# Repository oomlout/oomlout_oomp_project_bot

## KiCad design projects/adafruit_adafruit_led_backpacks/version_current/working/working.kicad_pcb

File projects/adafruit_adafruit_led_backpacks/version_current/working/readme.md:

# OOMP Project  
## Adafruit-LED-Backpacks  by adafruit  
  
oomp key: oomp_projects_flat_adafruit_adafruit_led_backpacks  
(snippet of original readme)  
  
- Adafruit LED Matrix backpacks PCBs  
  
&nbsp;   
&nbsp;   
&nbsp;   
<br />  
&nbsp;   
&nbsp;   
&nbsp;   
<br />  
  
What's better than a single LED? Lots of LEDs! A fun way to make a small display is to use an 8x8 matrix or a 4-digit 7-segment display. Matrices like these are 'multiplexed' - so to control all the seven-segment LEDs you need 14 pins. That's a lot of pins, and there are driver chips like the MAX7219 that can control a matrix for you but there's a lot of wiring to set up and they take up a ton of space. Here at Adafruit we feel your pain! After all, wouldn't it be awesome if you could control a matrix without tons of wiring? That's where these adorable LED matrix backpacks come in. We have  
  full source readme at [readme_src.md](readme_src.md)  
  
source repo at: [https://github.com/adafruit/Adafruit-LED-Backpacks](https://github.com/adafruit/Adafruit-LED-Backpacks)  
## Board  

## Schematic  

[schematic pdf](working_schematic.pdf)  
## Images

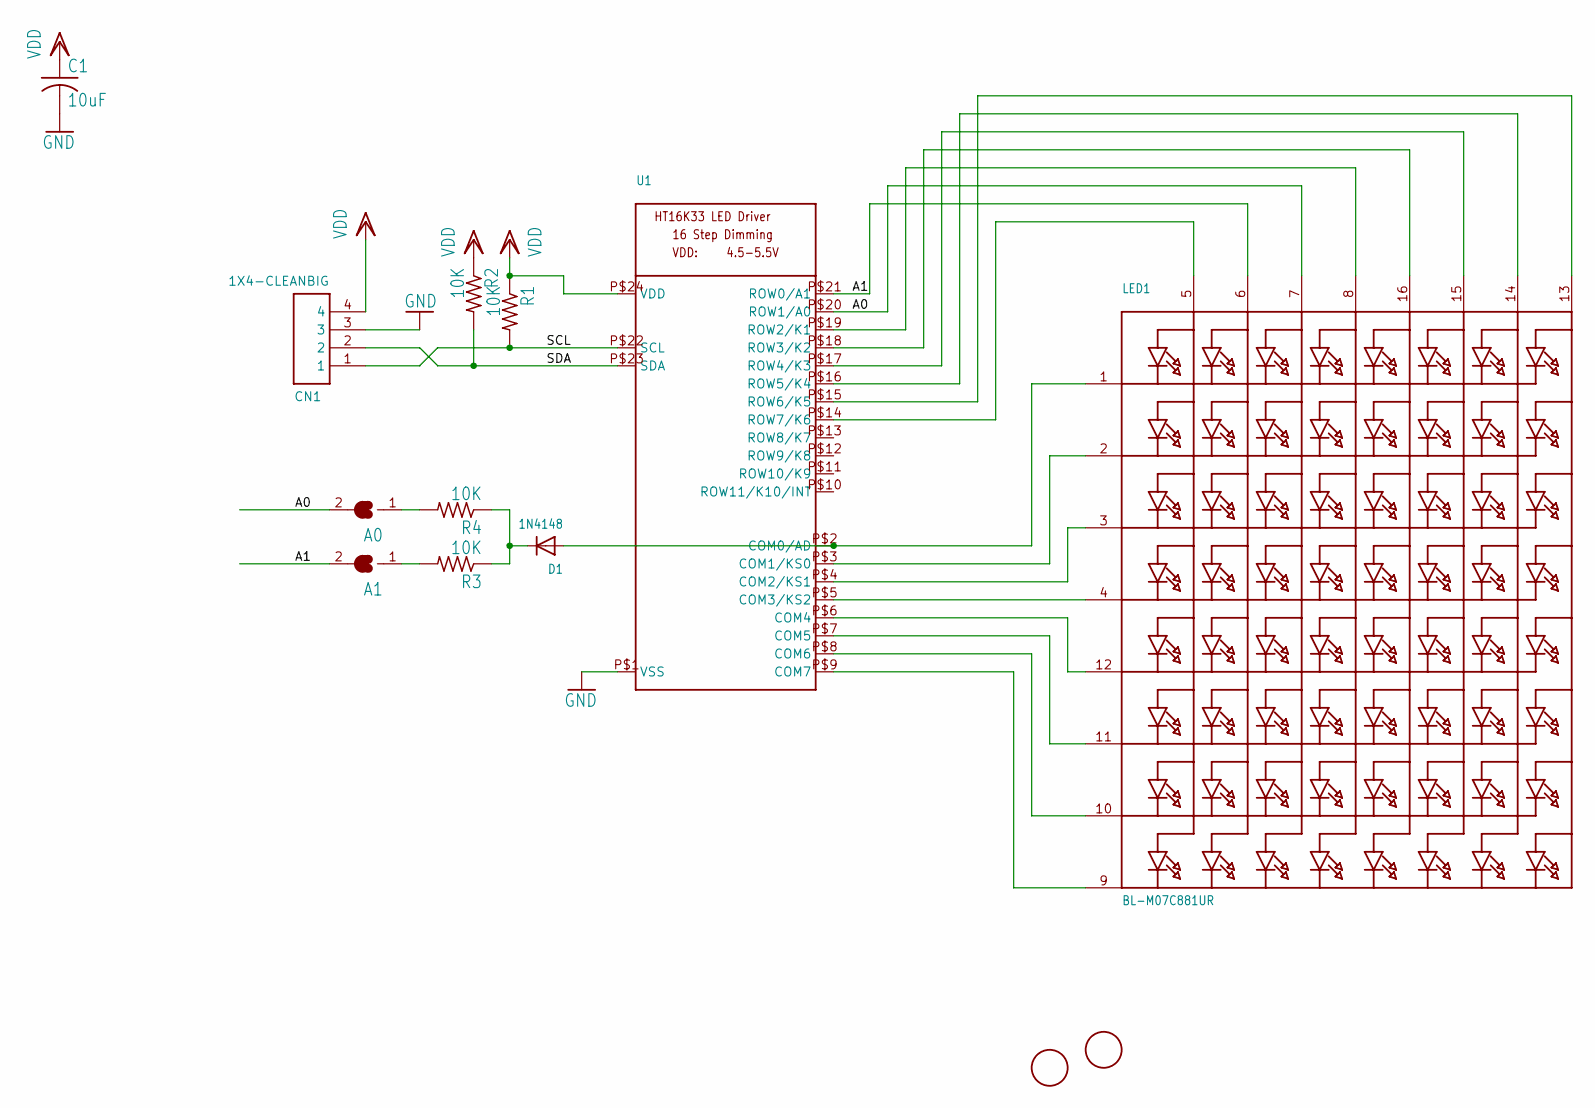
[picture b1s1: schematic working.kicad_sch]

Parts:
A0, A1: SOLDERJUMPERREFLOW_NOPASTE; SOLDERJUMPER_REFLOW_NOPASTE
C1: 10uF; C0805
CN1: 1X4-CLEANBIG; 1X04-CLEANBIG
D1: 1N4148; SOD-323F
LED1: BL-M07C881UR; SEGMENT_BL-M07C881UR
R1, R2, R3, R4: 10K; R0805
U1: HT16K33_SOP24; SOP24_300MIL
U$1, U$2: FIDUCIAL; FIDUCIAL_1MM

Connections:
A0: A0.2, LED1.7 (A3), U1.P$20 (ROW1/A0)
A1: A1.2, LED1.6 (A2), U1.P$21 (ROW0/A1)
GND: C1.2, CN1.3, U1.P$1 (VSS)
unnamed: LED1.9 (K8), U1.P$9 (COM7)
unnamed: LED1.10 (K7), U1.P$8 (COM6)
unnamed: LED1.11 (K6), U1.P$7 (COM5)
unnamed: LED1.12 (K5), U1.P$6 (COM4)
unnamed: LED1.4 (K4), U1.P$5 (COM3/KS2)
unnamed: LED1.3 (K3), U1.P$4 (COM2/KS1)
unnamed: LED1.2 (K2), U1.P$3 (COM1/KS0)
unnamed: D1.A, LED1.1 (K1), U1.P$2 (COM0/AD)
unnamed: LED1.8 (A4), U1.P$19 (ROW2/K1)
unnamed: LED1.16 (A5), U1.P$18 (ROW3/K2)
unnamed: LED1.15 (A6), U1.P$17 (ROW4/K3)
unnamed: D1.C, R3.1, R4.1
unnamed: LED1.5 (A1), U1.P$14 (ROW7/K6)
unnamed: A1.1, R3.2
unnamed: A0.1, R4.2
SCL: CN1.1, R1.2, U1.P$22 (SCL)
SDA: CN1.2, R2.2, U1.P$23 (SDA)
SEG_F: LED1.14 (A7), U1.P$16 (ROW5/K4)
SEG_G: LED1.13 (A8), U1.P$15 (ROW6/K5)
VDD: C1.1, CN1.4, R1.1, R2.1, U1.P$24 (VDD)

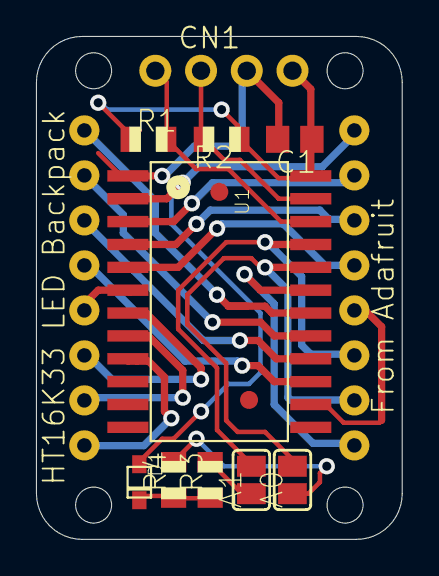
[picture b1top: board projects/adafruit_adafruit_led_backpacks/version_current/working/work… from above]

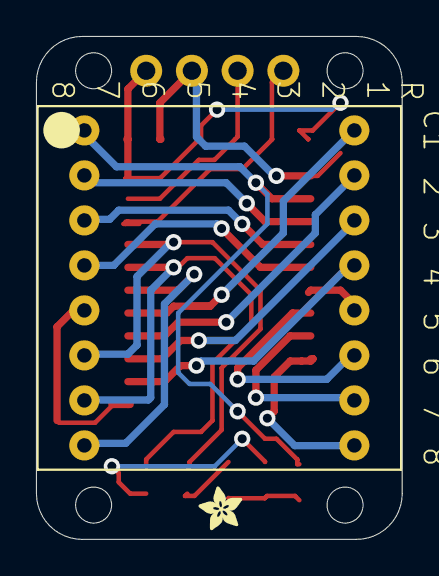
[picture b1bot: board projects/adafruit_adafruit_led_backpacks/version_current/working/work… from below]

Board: 16 copper layers, 20.3 x 27.9 mm, 18 parts (2 on the bottom side), 23 nets.

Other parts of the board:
@HOLE0, @HOLE1, @HOLE2, @HOLE3: (no value)
U$4: ADAFRUIT_2.5MM

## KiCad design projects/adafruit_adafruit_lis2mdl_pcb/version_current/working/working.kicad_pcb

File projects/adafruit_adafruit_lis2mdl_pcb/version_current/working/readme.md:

# OOMP Project  
## Adafruit-LIS2MDL-PCB  by adafruit  
  
oomp key: oomp_projects_flat_adafruit_adafruit_lis2mdl_pcb  
(snippet of original readme)  
  
-- Adafruit LIS2MDL 3-Axis Magnetometer PCB  
  
<a href="http://www.adafruit.com/products/4488"><br/>  
Click here to purchase one from the Adafruit shop</a>  
  
PCB files for the Adafruit LIS2MDL 3-Axis Magnetometer.   
  
Format is EagleCAD schematic and board layout  
* https://www.adafruit.com/product/4488  
  
--- Description  
  
Sense the magnetic fields that surround us with this handy triple-axis magnetometer (compass) module. Magnetometers can sense where the strongest magnetic force is coming from, generally used to detect magnetic north, but can also be used for measuring magnetic fields. This sensor tends to be paired with a 6-DoF (degree of freedom) accelerometer/gyroscope to create a 9-DoF inertial measurement unit that can detect its orientation in real-space thanks to Earth's stable magnetic field. It's a great match for any of our 6-DoF IMU sensors such as the LSM6DSOX or LSM6DS33.  
  
--- License  
  
Adafruit invests time and resources providing this open source design, please support Adafruit and open-source hardware by purchasing products from [Adafruit](https://www.adafruit.com)!  
  
Designed by Limor Fried/Ladyada for Adafruit Industries.  
  
Creative Commons Attribution/Share-Alike, all text above must be included in any redistribution.   
See license.txt for additional details.  
  
  full source readme at [readme_src.md](readme_src.md)  
  
source repo at: [https://github.com/adafruit/Adafruit-LIS2MDL-PCB](https://github.com/adafruit/Adafruit-LIS2MDL-PCB)  
## Board  

## Schematic  

[schematic pdf](working_schematic.pdf)  
## Images

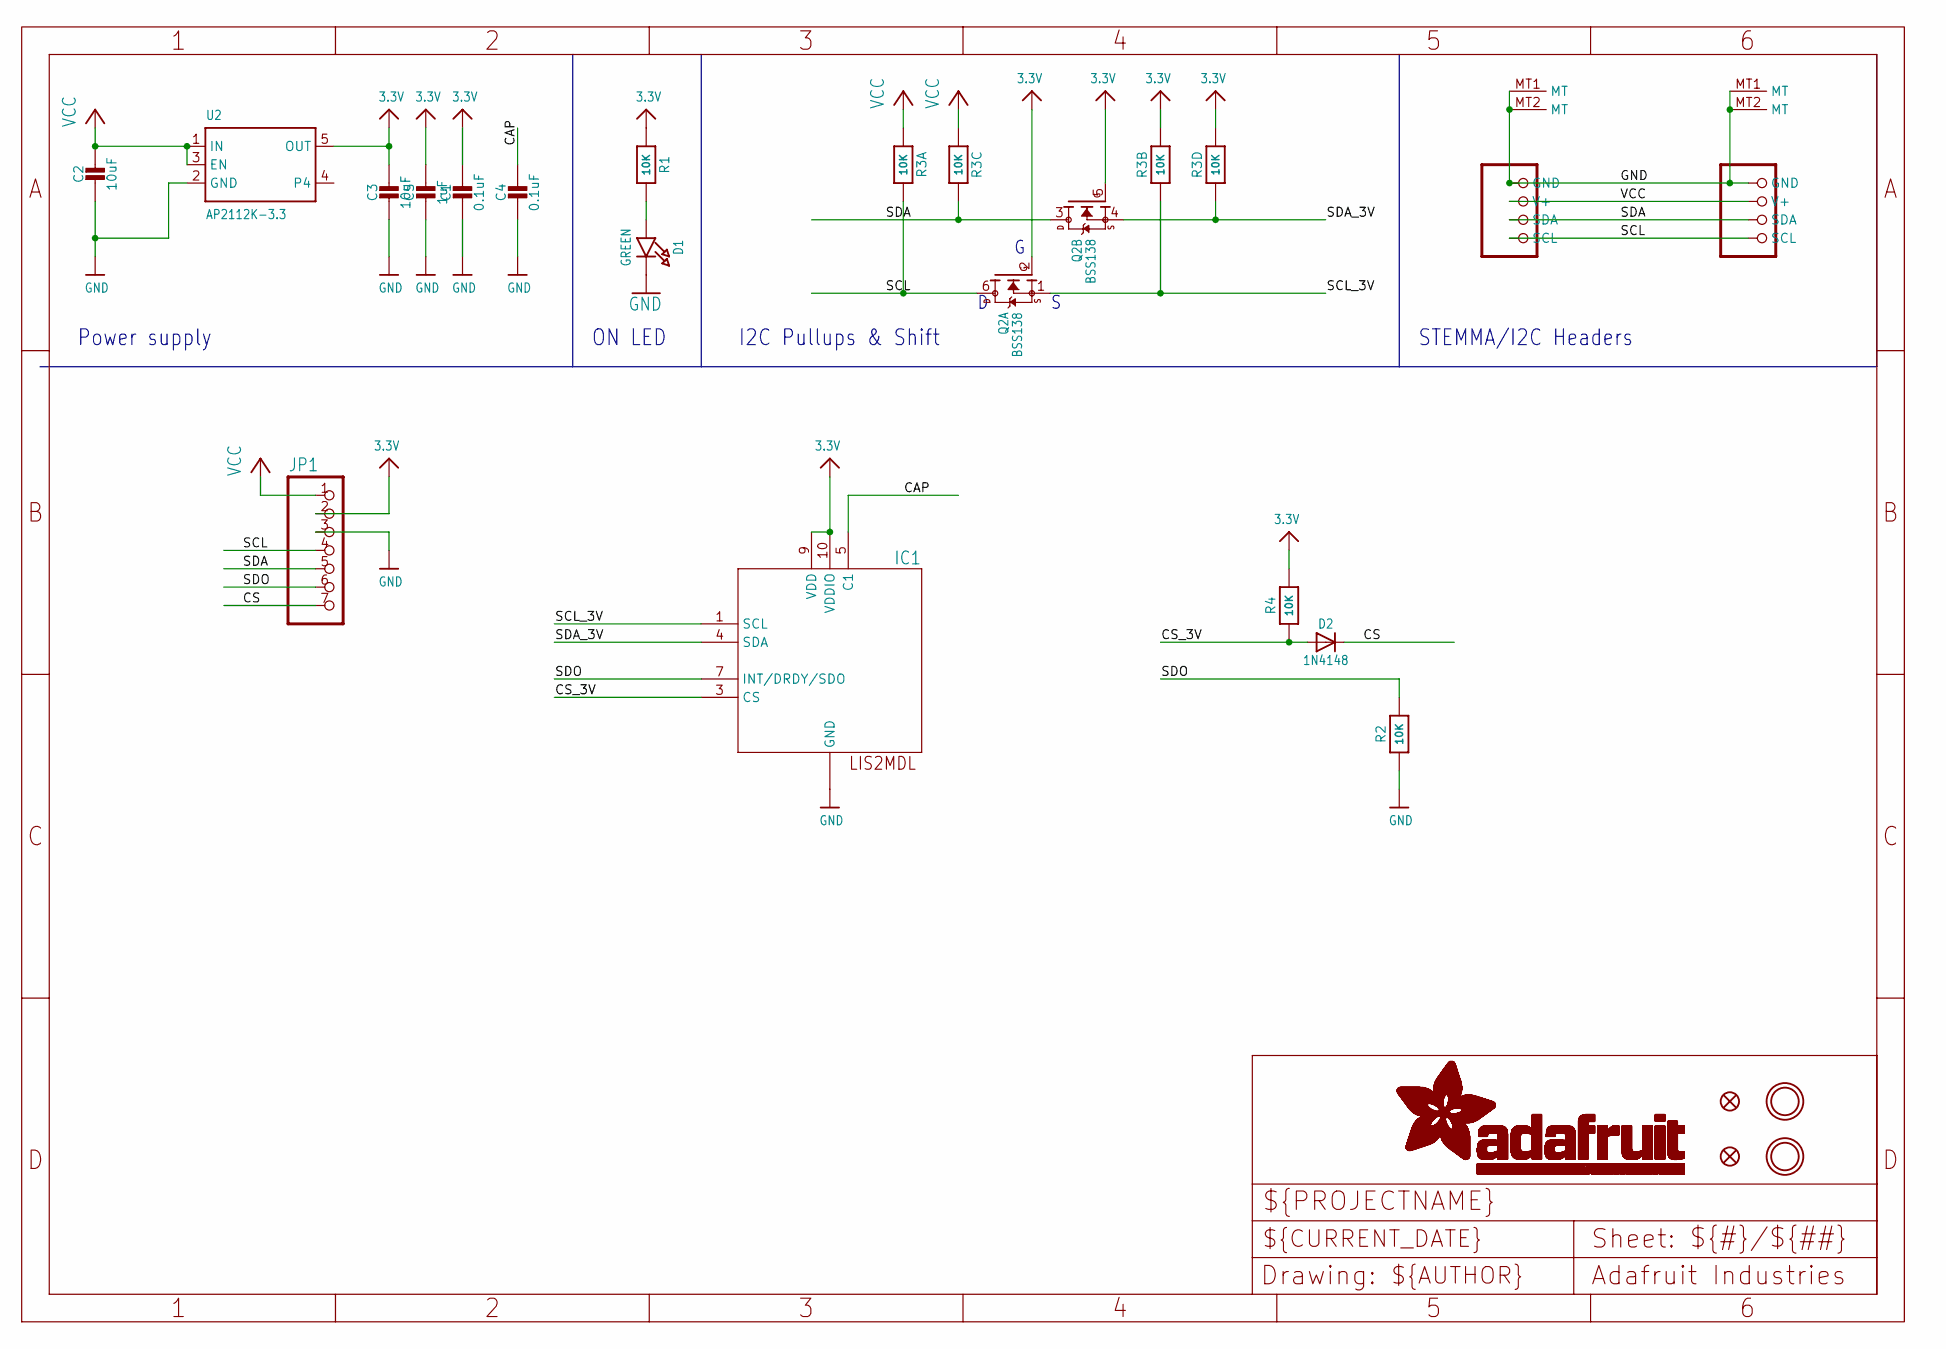
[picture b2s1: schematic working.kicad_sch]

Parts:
C1, C4: 0.1uF; 0603-NO
C2, C3: 10uF; 0805-NO
C5: 1uF; 0603-NO
CONN3, CONN4: STEMMA_I2C_QT; JST_SH4
D1: GREEN; CHIPLED_0603_NOOUTLINE
D2: 1N4148; SOD-323
FID3, FID4: FIDUCIAL_1MM
IC1: LIS2MDL; LGA12_2X2MM
JP1: HEADER-1X770MIL; 1X07_ROUND_70
Q2: BSS138; SOT363
R1, R2, R4: 10K; 0603-NO
R3: 10K; RESPACK_4X0603
U2: AP2112K-3.3; SOT23-5
U$1, U$17: MOUNTINGHOLE2.5; MOUNTINGHOLE_2.5_PLATED

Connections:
3.3V: C1.1, C3.1, C5.1, IC1.9 (VDD), IC1.10 (VDDIO), JP1.2, Q2.2 (G), Q2.5 (G), R1.1, R3.2 (1), R3.4 (1), R4.2, U2.5 (OUT)
CAP: C4.1, IC1.5 (C1)
CS: D2.C, JP1.7
CS_3V: D2.A, IC1.3 (CS), R4.1
GND: C1.2, C2.2, C3.2, C4.2, C5.2, CONN3.1 (GND), CONN3.MT1 (MT), CONN3.MT2 (MT), CONN4.1 (GND), CONN4.MT1 (MT), CONN4.MT2 (MT), D1.C, IC1.2 (GND), IC1.6 (GND), IC1.8 (GND), IC1.11 (GND), IC1.12 (GND), JP1.3, R2.1, U2.2 (GND)
unnamed: D1.A, R1.2
SCL: CONN3.4 (SCL), CONN4.4 (SCL), JP1.4, Q2.6 (D), R3.8 (2)
SCL_3V: IC1.1 (SCL), Q2.1 (S), R3.7 (2)
SDA: CONN3.3 (SDA), CONN4.3 (SDA), JP1.5, Q2.3 (D), R3.6 (2)
SDA_3V: IC1.4 (SDA), Q2.4 (S), R3.5 (2)
SDO: IC1.7 (INT/DRDY/SDO), JP1.6, R2.2
VCC: C2.1, CONN3.2 (V+), CONN4.2 (V+), JP1.1, R3.1, R3.3 (1), U2.1 (IN), U2.3 (EN)

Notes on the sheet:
Power supply
ON LED
I2C Pullups & Shift
STEMMA/I2C Headers

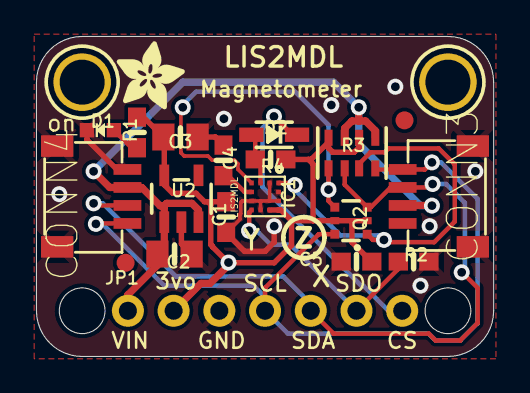
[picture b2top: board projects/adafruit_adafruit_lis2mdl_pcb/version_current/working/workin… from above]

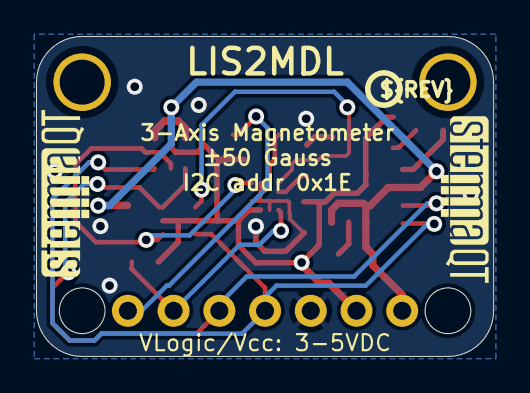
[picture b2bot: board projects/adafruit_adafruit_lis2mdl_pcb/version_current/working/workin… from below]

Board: 2 copper layers, 25.4 x 17.8 mm, 27 parts (3 on the bottom side), 12 nets.

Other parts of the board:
@HOLE0, @HOLE1: (no value)
U$11: ADAFRUIT_3.5MM
U$25: PCBFEAT-REV-040
U$30, U$31: STEMMAQT

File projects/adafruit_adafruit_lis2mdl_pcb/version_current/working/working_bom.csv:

Row,Description,Part,References,Value,Footprint,Quantity Per PCB,Status,Datasheet
1,,CAP_CERAMIC0603_NO,C1 C4,0.1uF,0603-NO,2, ,
2,,CAP_CERAMIC0603_NO,C5,1uF,0603-NO,1, ,
3,,CAP_CERAMIC0805-NOOUTLINE,C2 C3,10uF,0805-NO,2, ,
4,,STEMMA_I2C_QT,CONN3 CONN4,STEMMA_I2C_QT,JST_SH4,2, ,
5,,DIODESOD-323,D2,1N4148,SOD-323,1, ,
6,,LED0603_NOOUTLINE,D1,GREEN,CHIPLED_0603_NOOUTLINE,1, ,
7,,LIS2MDL,IC1,LIS2MDL,LGA12_2X2MM,1, ,
8,,HEADER-1X770MIL,JP1,HEADER-1X770MIL,1X07_ROUND_70,1, ,
9,,MOSFET-N_DUAL,Q2,BSS138,SOT363,1, ,
10,,RESISTOR_0603_NOOUT,R1 R2 R4,10K,0603-NO,3, ,
11,,RESISTOR_4PACK,R3,10K,RESPACK_4X0603,1, ,
12,,VREG_SOT23-5,U2,AP2112K-3.3,SOT23-5,1, ,





Project info:
Schematic:,working
Variant:,default
Revision:,
Date:,2023-08-03_17-21-22
KiCad Version:,7.0.6-7.0.6~ubuntu22.04.1
Statistics:
Component Groups:,12
Component Count:,17 (0 SMD/ 0 THT)
Fitted Components:,17 (0 SMD/ 0 THT)
Number of PCBs:,1
Total Components:,17

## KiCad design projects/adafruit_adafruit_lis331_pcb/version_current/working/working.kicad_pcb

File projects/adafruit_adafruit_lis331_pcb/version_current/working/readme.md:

# Adafruit-LIS331-PCB by adafruit  
This is a harvested standardized copy of a project from github.  
The original project can be found at:  
https://github.com/adafruit/Adafruit-LIS331-PCB  
Please consult that link for additional, details, files, and license information.  
Note: It was auto harvested and if the original repo had more than one board file or anything out of the ordinary the files here are likely not representative.

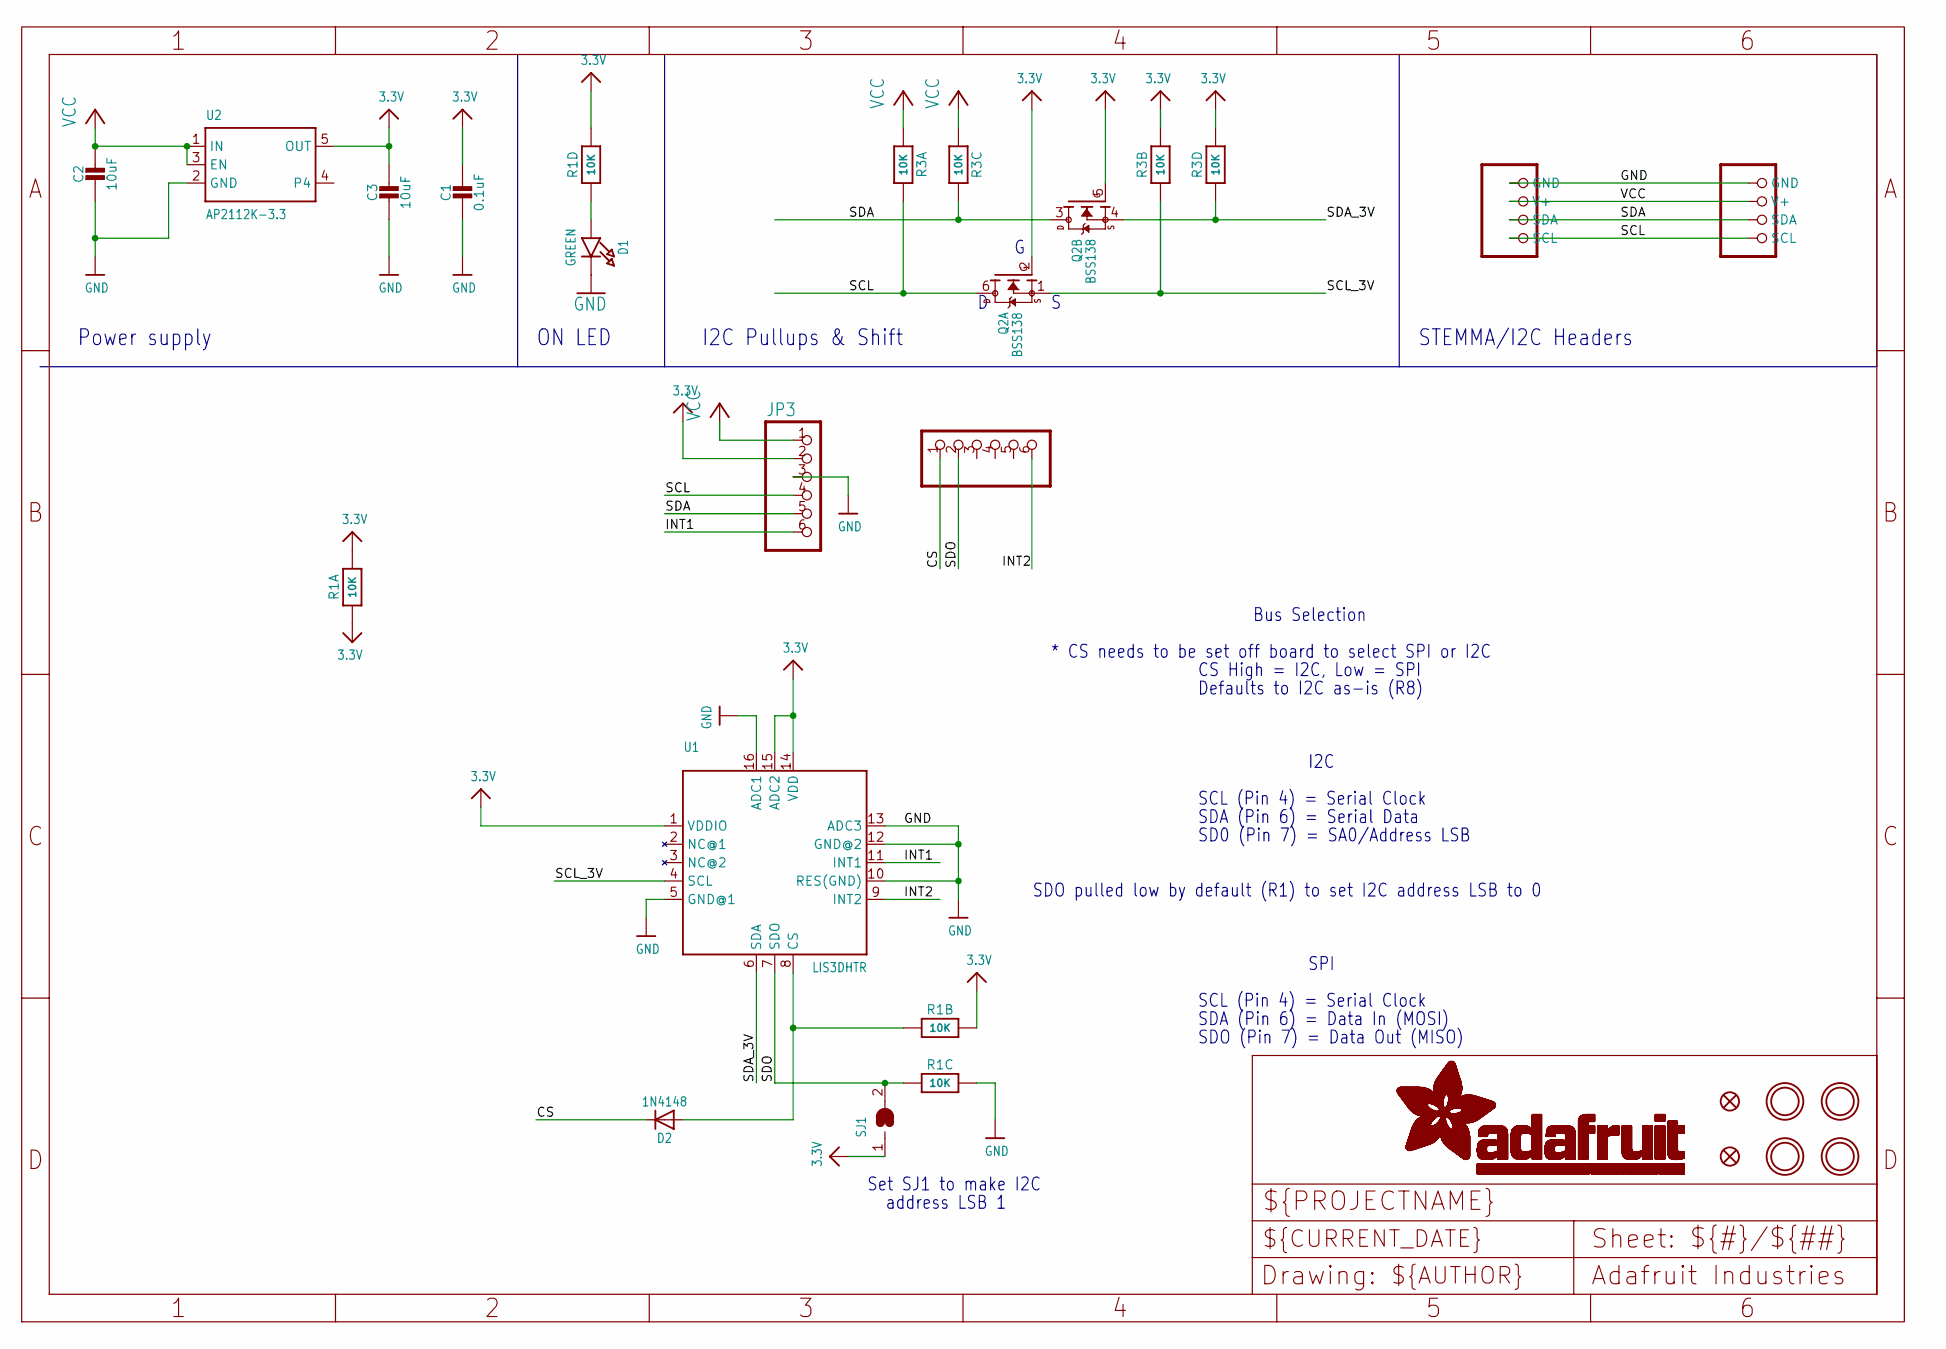
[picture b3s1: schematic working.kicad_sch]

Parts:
C1: 0.1uF; 0603-NO
C2, C3: 10uF; 0805-NO
CONN3, CONN4: STEMMA_I2C_QT; JST_SH4
D1: GREEN; CHIPLED_0603_NOOUTLINE
D2: 1N4148; SOD-323
FID3, FID4: FIDUCIAL_1MM
JP2, JP3: HEADER-1X670MIL; 1X06_ROUND_70
Q2: BSS138; SOT363
R1, R3: 10K; RESPACK_4X0603
SJ1: SOLDERJUMPER; SOLDERJUMPER_ARROW_NOPASTE
U1: LIS3DHTR; LGA16_3X3MM
U2: AP2112K-3.3; SOT23-5
U$1, U$17, U$19, U$21: MOUNTINGHOLE2.5; MOUNTINGHOLE_2.5_PLATED

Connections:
3.3V: C1.1, C3.1, JP3.2, Q2.2 (G), Q2.5 (G), R1.1, R1.5 (2), R1.7 (2), R1.8 (2), R3.2 (1), R3.4 (1), SJ1.1, U1.1 (VDDIO), U1.14 (VDD), U1.15 (ADC2), U2.5 (OUT)
CS: D2.C, JP2.1
GND: C1.2, C2.2, C3.2, CONN3.1 (GND), CONN4.1 (GND), D1.C, JP3.3, R1.6 (2), U1.5 (GND@1), U1.10 (RES(GND)), U1.12 (GND@2), U1.13 (ADC3), U1.16 (ADC1), U2.2 (GND)
INT1: JP3.6, U1.11 (INT1)
INT2: JP2.6, U1.9 (INT2)
unnamed: D1.A, R1.4 (1)
unnamed: D2.A, R1.2 (1), U1.8 (CS)
SCL: CONN3.4 (SCL), CONN4.4 (SCL), JP3.4, Q2.6 (D), R3.8 (2)
SCL_3V: Q2.1 (S), R3.7 (2), U1.4 (SCL)
SDA: CONN3.3 (SDA), CONN4.3 (SDA), JP3.5, Q2.3 (D), R3.6 (2)
SDA_3V: Q2.4 (S), R3.5 (2), U1.6 (SDA)
SDO: JP2.2, R1.3 (1), SJ1.2, U1.7 (SDO)
VCC: C2.1, CONN3.2 (V+), CONN4.2 (V+), JP3.1, R3.1, R3.3 (1), U2.1 (IN), U2.3 (EN)

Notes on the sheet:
Bus Selection
SDO pulled low by default (R1) to set I2C address LSB to 0
SDA (Pin 6) = Serial Data
* CS needs to be set off board to select SPI or I2C
SCL (Pin 4) = Serial Clock
SPI
SD0 (Pin 7) = SA0/Address LSB
ON LED
SDA (Pin 6) = Data In (MOSI)
Defaults to I2C as-is (R8)
SDO (Pin 7) = Data Out (MISO)
Power supply
CS High = I2C, Low = SPI
I2C
Set SJ1 to make I2C
STEMMA/I2C Headers
address LSB 1
I2C Pullups & Shift

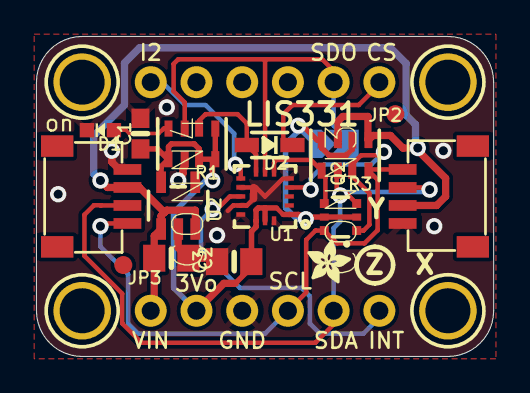
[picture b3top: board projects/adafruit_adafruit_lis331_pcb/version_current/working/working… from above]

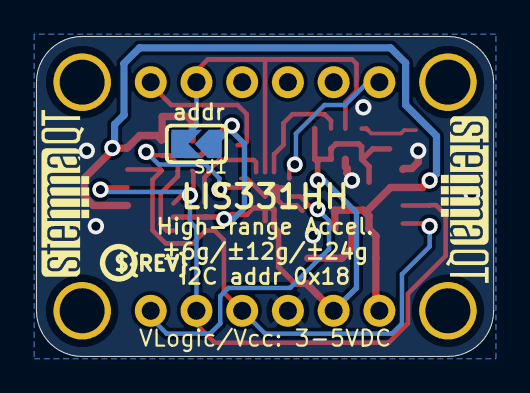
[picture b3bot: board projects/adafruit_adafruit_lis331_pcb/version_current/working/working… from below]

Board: 2 copper layers, 25.4 x 17.8 mm, 25 parts (4 on the bottom side), 13 nets.

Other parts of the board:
U$12: ADAFRUIT_2.5MM
U$25: PCBFEAT-REV-040
U$30, U$31: STEMMAQT

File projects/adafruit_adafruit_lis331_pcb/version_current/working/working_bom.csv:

"Id";"Designator";"Footprint";"Quantity";"Designation";"Supplier and ref";
1;"U1";"LGA16_3X3MM";1;"LIS3DHTR";;;
2;"C1";"0603-NO";1;"0.1uF";;;
3;"C3,C2";"0805-NO";2;"10uF";;;
4;"CONN3,CONN4";"JST_SH4";2;"STEMMA_I2C_QT";;;
5;"R1,R3";"RESPACK_4X0603";2;"10K";;;
6;"U2";"SOT23-5";1;"AP2112K-3.3";;;
7;"JP2,JP3";"1X06_ROUND_70";2;"";;;
8;"FID3,FID4";"FIDUCIAL_1MM";2;"FIDUCIAL_1MM";;;
9;"Q2";"SOT363";1;"BSS138";;;
10;"U$19,U$1,U$21,U$17";"MOUNTINGHOLE_2.5_PLATED";4;"MOUNTINGHOLE2.5";;;
11;"D2";"SOD-323";1;"1N4148";;;
12;"D1";"CHIPLED_0603_NOOUTLINE";1;"GREEN";;;
13;"U$12";"ADAFRUIT_2.5MM";1;"";;;
14;"U$30,U$31";"STEMMAQT";2;"";;;
15;"SJ1";"SOLDERJUMPER_ARROW_NOPASTE";1;"";;;
16;"U$25";"PCBFEAT-REV-040";1;"";;;

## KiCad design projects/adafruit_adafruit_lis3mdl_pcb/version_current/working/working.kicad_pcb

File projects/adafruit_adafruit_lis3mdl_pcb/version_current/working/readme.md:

# OOMP Project  
## Adafruit-LIS3MDL-PCB  by adafruit  
  
oomp key: oomp_projects_flat_adafruit_adafruit_lis3mdl_pcb  
(snippet of original readme)  
  
-- Adafruit LIS3MDL Triple-axis Magnetometer PCB  
  
<a href="http://www.adafruit.com/products/4479"><br/>  
Click here to purchase one from the Adafruit shop</a>  
  
PCB files for the Adafruit LIS3MDL Triple-axis Magnetometer.   
  
Format is EagleCAD schematic and board layout  
* https://www.adafruit.com/product/4479  
  
--- Description  
  
Sense the magnetic fields that surround us with this handy triple-axis magnetometer (compass) module. Magnetometers can sense where the strongest magnetic force is coming from, generally used to detect magnetic north, but can also be used for measuring magnetic fields. This sensor tends to be paired with a 6-DoF (degree of freedom) accelerometer/gyroscope to create a 9-DoF inertial measurement unit that can detect its orientation in real-space thanks to Earth's stable magnetic field. It's a great match for the LSM6DSOX from ST!  
  
We based this breakout on ST's LIS3MDL, a great general purpose magnetometer. This compact sensor uses I2C to communicate and its very easy to use. Simply download our library and connect the SCL pin to your I2C clock pin, and SDA pin to your I2C data pin and upload our test program to read out magnetic field data. If you'd like, you can also use SPI to receive data (we just happen to prefer I2C here)  
  
This sensor can sense ranges from +-4 gauss (+- 400 uTesla) up to +-16 gauss (+- 16uTesla). For ultra high precision, 155 Hz update rate is recommended - but if you don't mind a littl  
  full source readme at [readme_src.md](readme_src.md)  
  
source repo at: [https://github.com/adafruit/Adafruit-LIS3MDL-PCB](https://github.com/adafruit/Adafruit-LIS3MDL-PCB)  
## Board  

## Schematic  

[schematic pdf](working_schematic.pdf)  
## Images

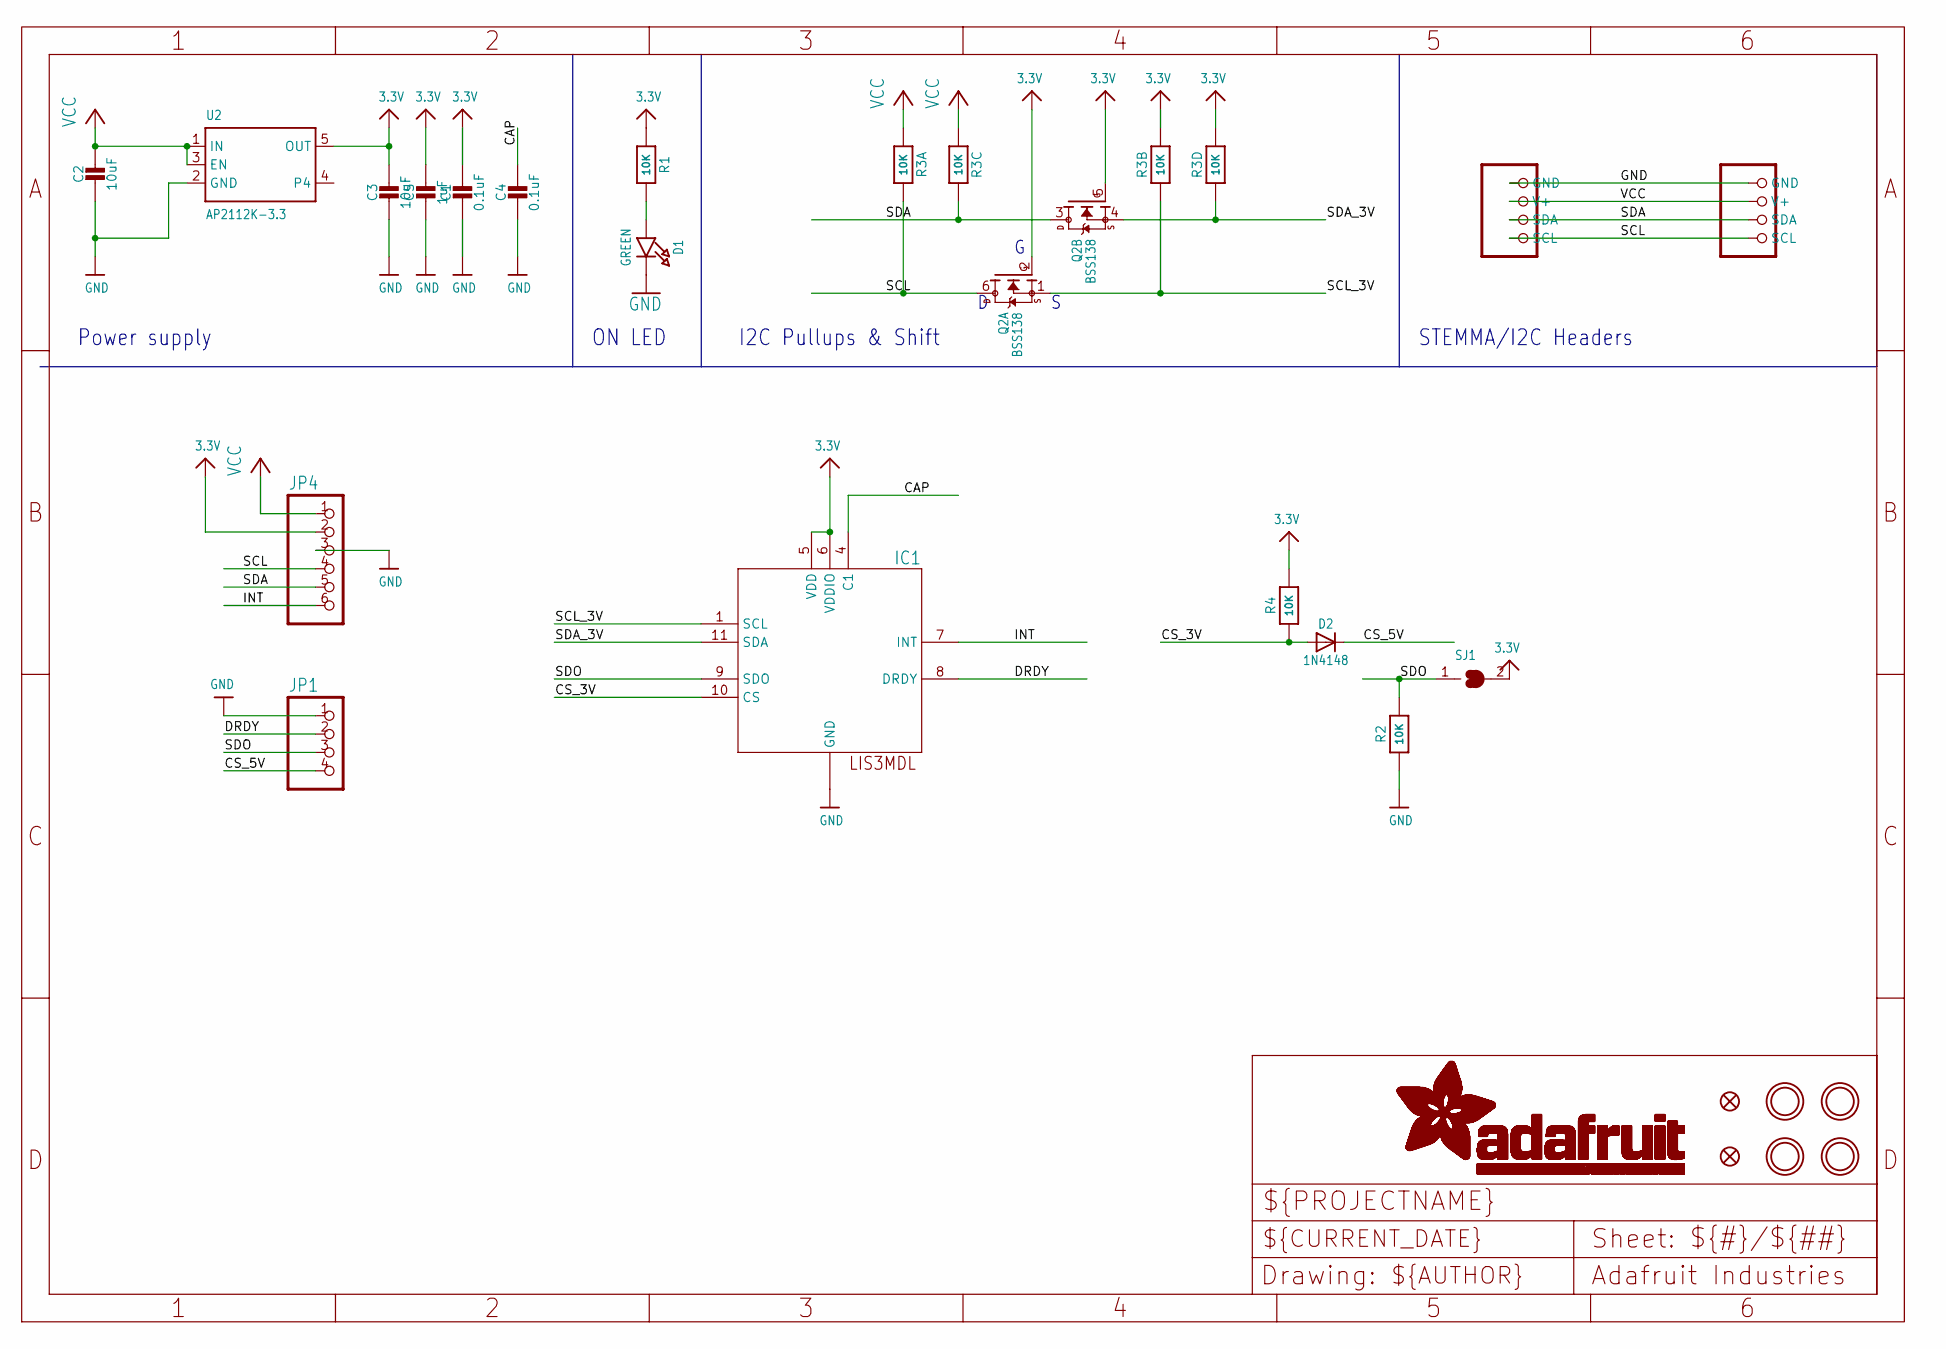
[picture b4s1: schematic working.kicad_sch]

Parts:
C1, C4: 0.1uF; 0603-NO
C2, C3: 10uF; 0805-NO
C5: 1uF; 0603-NO
CONN3, CONN4: STEMMA_I2C_QT; JST_SH4
D1: GREEN; CHIPLED_0603_NOOUTLINE
D2: 1N4148; SOD-323
FID3, FID4: FIDUCIAL_1MM
IC1: LIS3MDL; LGA12_2X2MM
JP1: HEADER-1X4ROUND; 1X04_ROUND
JP4: HEADER-1X670MIL; 1X06_ROUND_70
Q2: BSS138; SOT363
R1, R2, R4: 10K; 0603-NO
R3: 10K; RESPACK_4X0603
SJ1: SOLDERJUMPER; SOLDERJUMPER_ARROW_NOPASTE
U2: AP2112K-3.3; SOT23-5
U$1, U$17, U$19, U$21: MOUNTINGHOLE2.5; MOUNTINGHOLE_2.5_PLATED

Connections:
3.3V: C1.1, C3.1, C5.1, IC1.5 (VDD), IC1.6 (VDDIO), JP4.2, Q2.2 (G), Q2.5 (G), R1.1, R3.2 (1), R3.4 (1), R4.2, SJ1.2, U2.5 (OUT)
CAP: C4.1, IC1.4 (C1)
CS_3V: D2.A, IC1.10 (CS), R4.1
CS_5V: D2.C, JP1.4
DRDY: IC1.8 (DRDY), JP1.2
GND: C1.2, C2.2, C3.2, C4.2, C5.2, CONN3.1 (GND), CONN4.1 (GND), D1.C, IC1.2 (GND), IC1.3 (GND), IC1.12 (GND), JP1.1, JP4.3, R2.1, U2.2 (GND)
INT: IC1.7 (INT), JP4.6
unnamed: D1.A, R1.2
SCL: CONN3.4 (SCL), CONN4.4 (SCL), JP4.4, Q2.6 (D), R3.8 (2)
SCL_3V: IC1.1 (SCL), Q2.1 (S), R3.7 (2)
SDA: CONN3.3 (SDA), CONN4.3 (SDA), JP4.5, Q2.3 (D), R3.6 (2)
SDA_3V: IC1.11 (SDA), Q2.4 (S), R3.5 (2)
SDO: IC1.9 (SDO), JP1.3, R2.2, SJ1.1
VCC: C2.1, CONN3.2 (V+), CONN4.2 (V+), JP4.1, R3.1, R3.3 (1), U2.1 (IN), U2.3 (EN)

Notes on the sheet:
STEMMA/I2C Headers
ON LED
Power supply
I2C Pullups & Shift

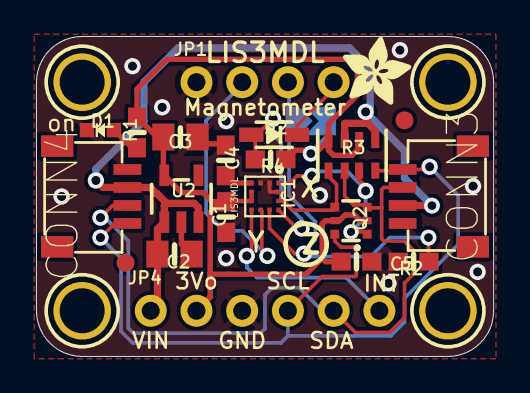
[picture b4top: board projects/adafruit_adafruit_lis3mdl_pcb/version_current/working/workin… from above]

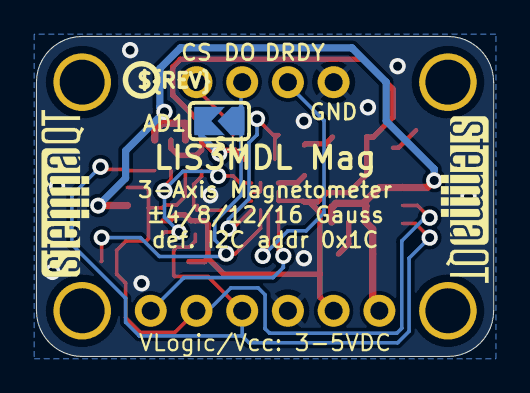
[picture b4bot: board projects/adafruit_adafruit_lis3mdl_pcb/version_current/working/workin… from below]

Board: 2 copper layers, 25.4 x 17.8 mm, 29 parts (4 on the bottom side), 14 nets.

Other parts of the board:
U$11: ADAFRUIT_3.5MM
U$25: PCBFEAT-REV-040
U$30, U$31: STEMMAQT

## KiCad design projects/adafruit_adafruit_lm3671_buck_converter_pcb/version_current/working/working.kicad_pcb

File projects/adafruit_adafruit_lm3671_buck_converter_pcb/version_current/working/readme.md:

# Adafruit-LM3671-Buck-Converter-PCB by adafruit  
This is a harvested standardized copy of a project from github.  
The original project can be found at:  
https://github.com/adafruit/Adafruit-LM3671-Buck-Converter-PCB  
Please consult that link for additional, details, files, and license information.  
Note: It was auto harvested and if the original repo had more than one board file or anything out of the ordinary the files here are likely not representative.

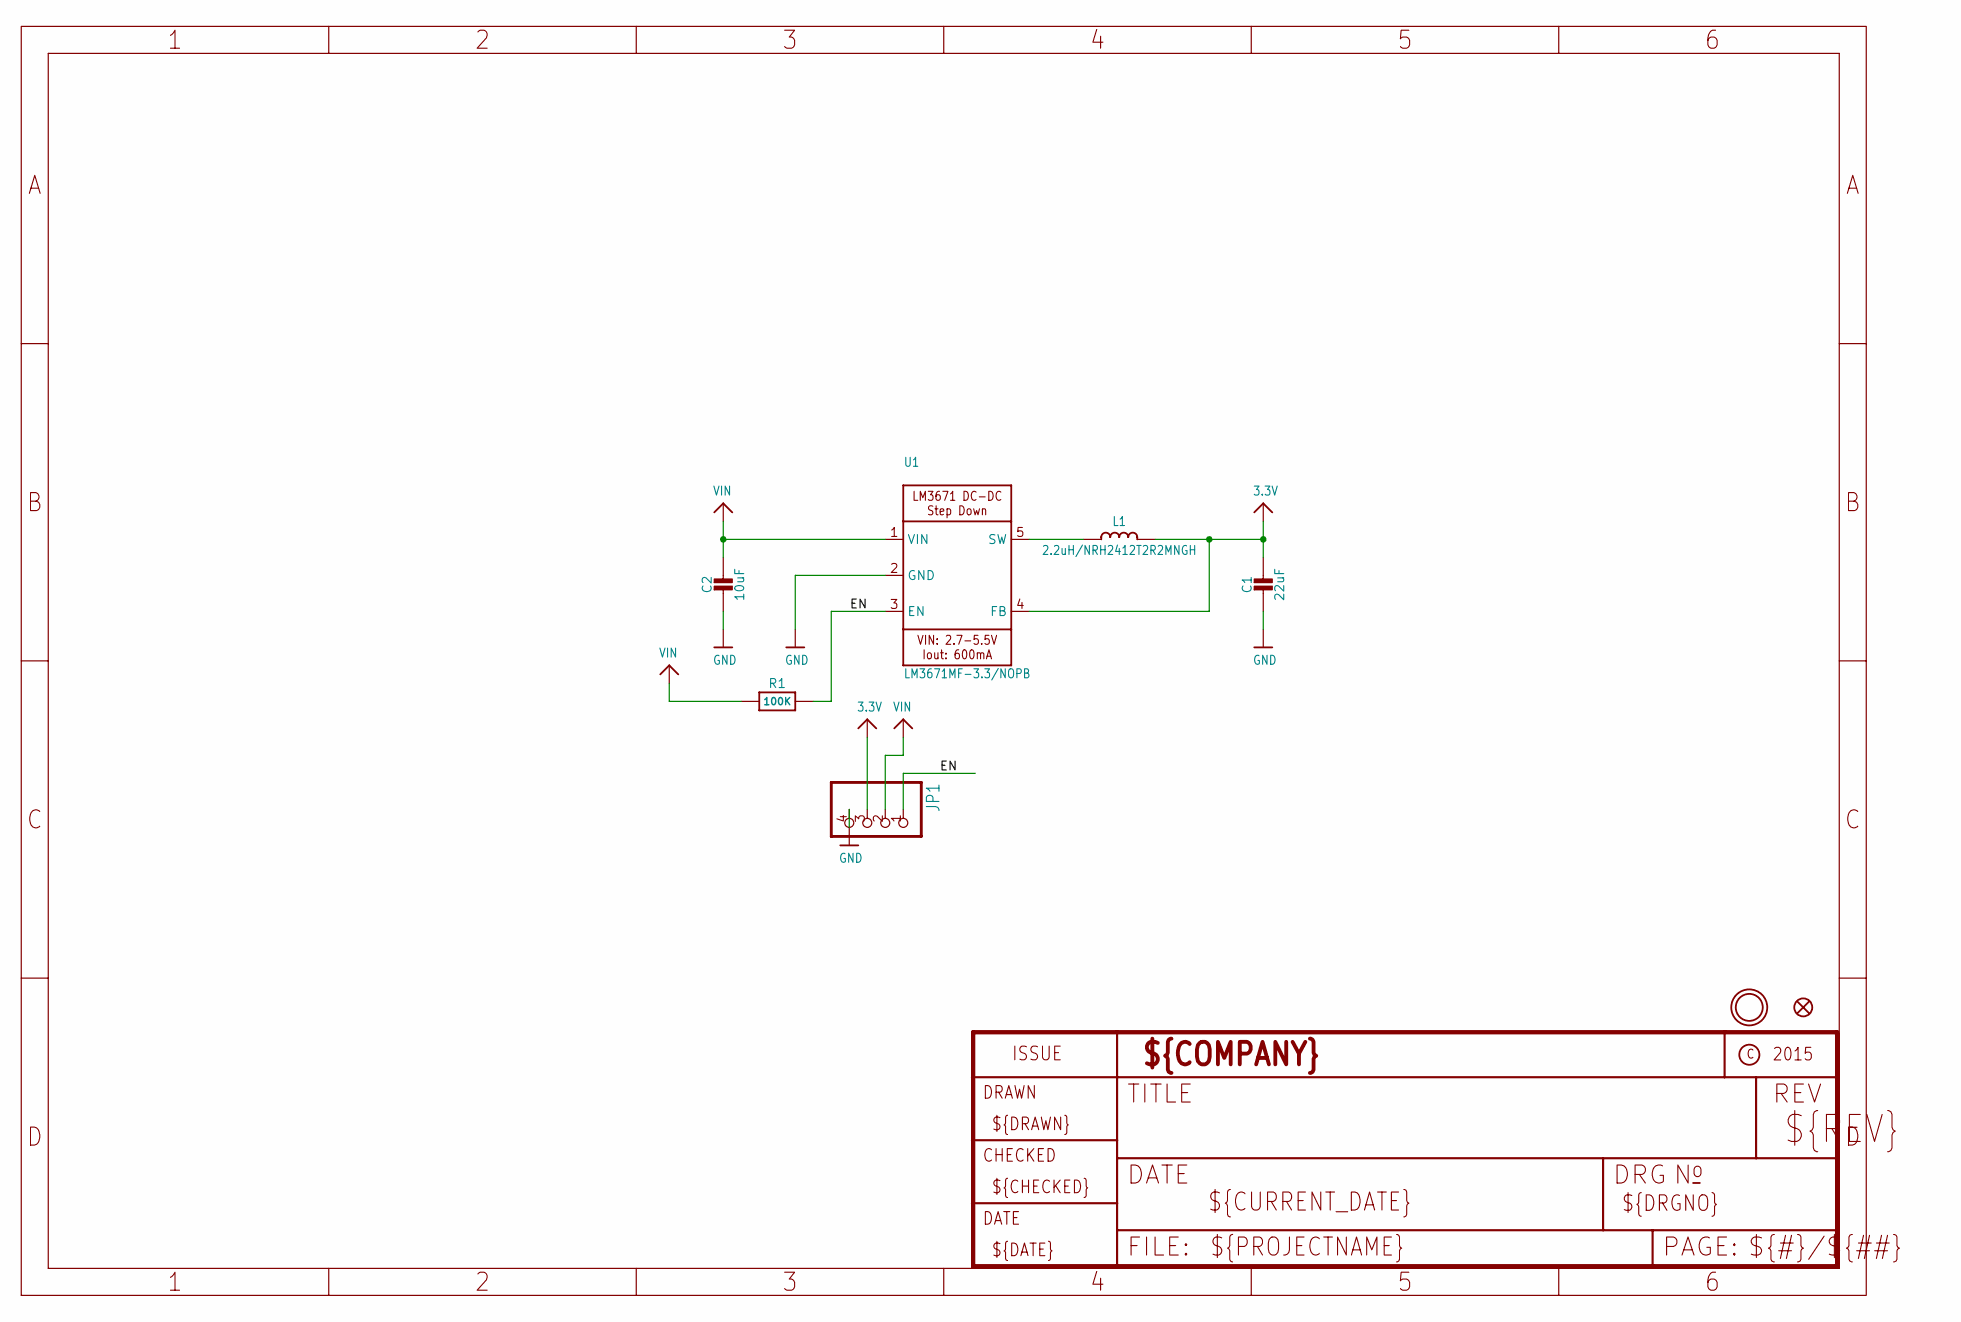
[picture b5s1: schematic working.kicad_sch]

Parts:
C1: 22uF; 0805-NO
C2: 10uF; 0805-NO
FID1: FIDUCIAL""; FIDUCIAL_1MM
JP1: HEADER-1X4ROUND; 1X04_ROUND
L1: 2.2uH/NRH2412T2R2MNGH; INDUCTOR_TAIYOYUDEN_NRH2412T
R1: 100K; 0805-NO
U1: LM3671MF-3.3/NOPB; SOT23-5
U$9: MOUNTINGHOLE2.5; MOUNTINGHOLE_2.5_PLATED

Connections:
3.3V: C1.1, JP1.3, L1.2, U1.4 (FB)
EN: JP1.1, R1.2, U1.3 (EN)
GND: C1.2, C2.2, JP1.4, U1.2 (GND)
unnamed: L1.1, U1.5 (SW)
VIN: C2.1, JP1.2, R1.1, U1.1 (VIN)

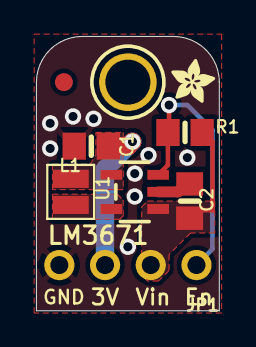
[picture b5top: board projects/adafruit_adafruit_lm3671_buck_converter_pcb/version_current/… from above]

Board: 2 copper layers, 10.2 x 15.2 mm, 10 parts (1 on the bottom side), 5 nets.

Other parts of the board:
U$10: PCBFEAT-REV-040
U$11: ADAFRUIT_2.5MM
